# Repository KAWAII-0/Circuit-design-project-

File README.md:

# Circuit-design-project-
project for circuit design class at PUT

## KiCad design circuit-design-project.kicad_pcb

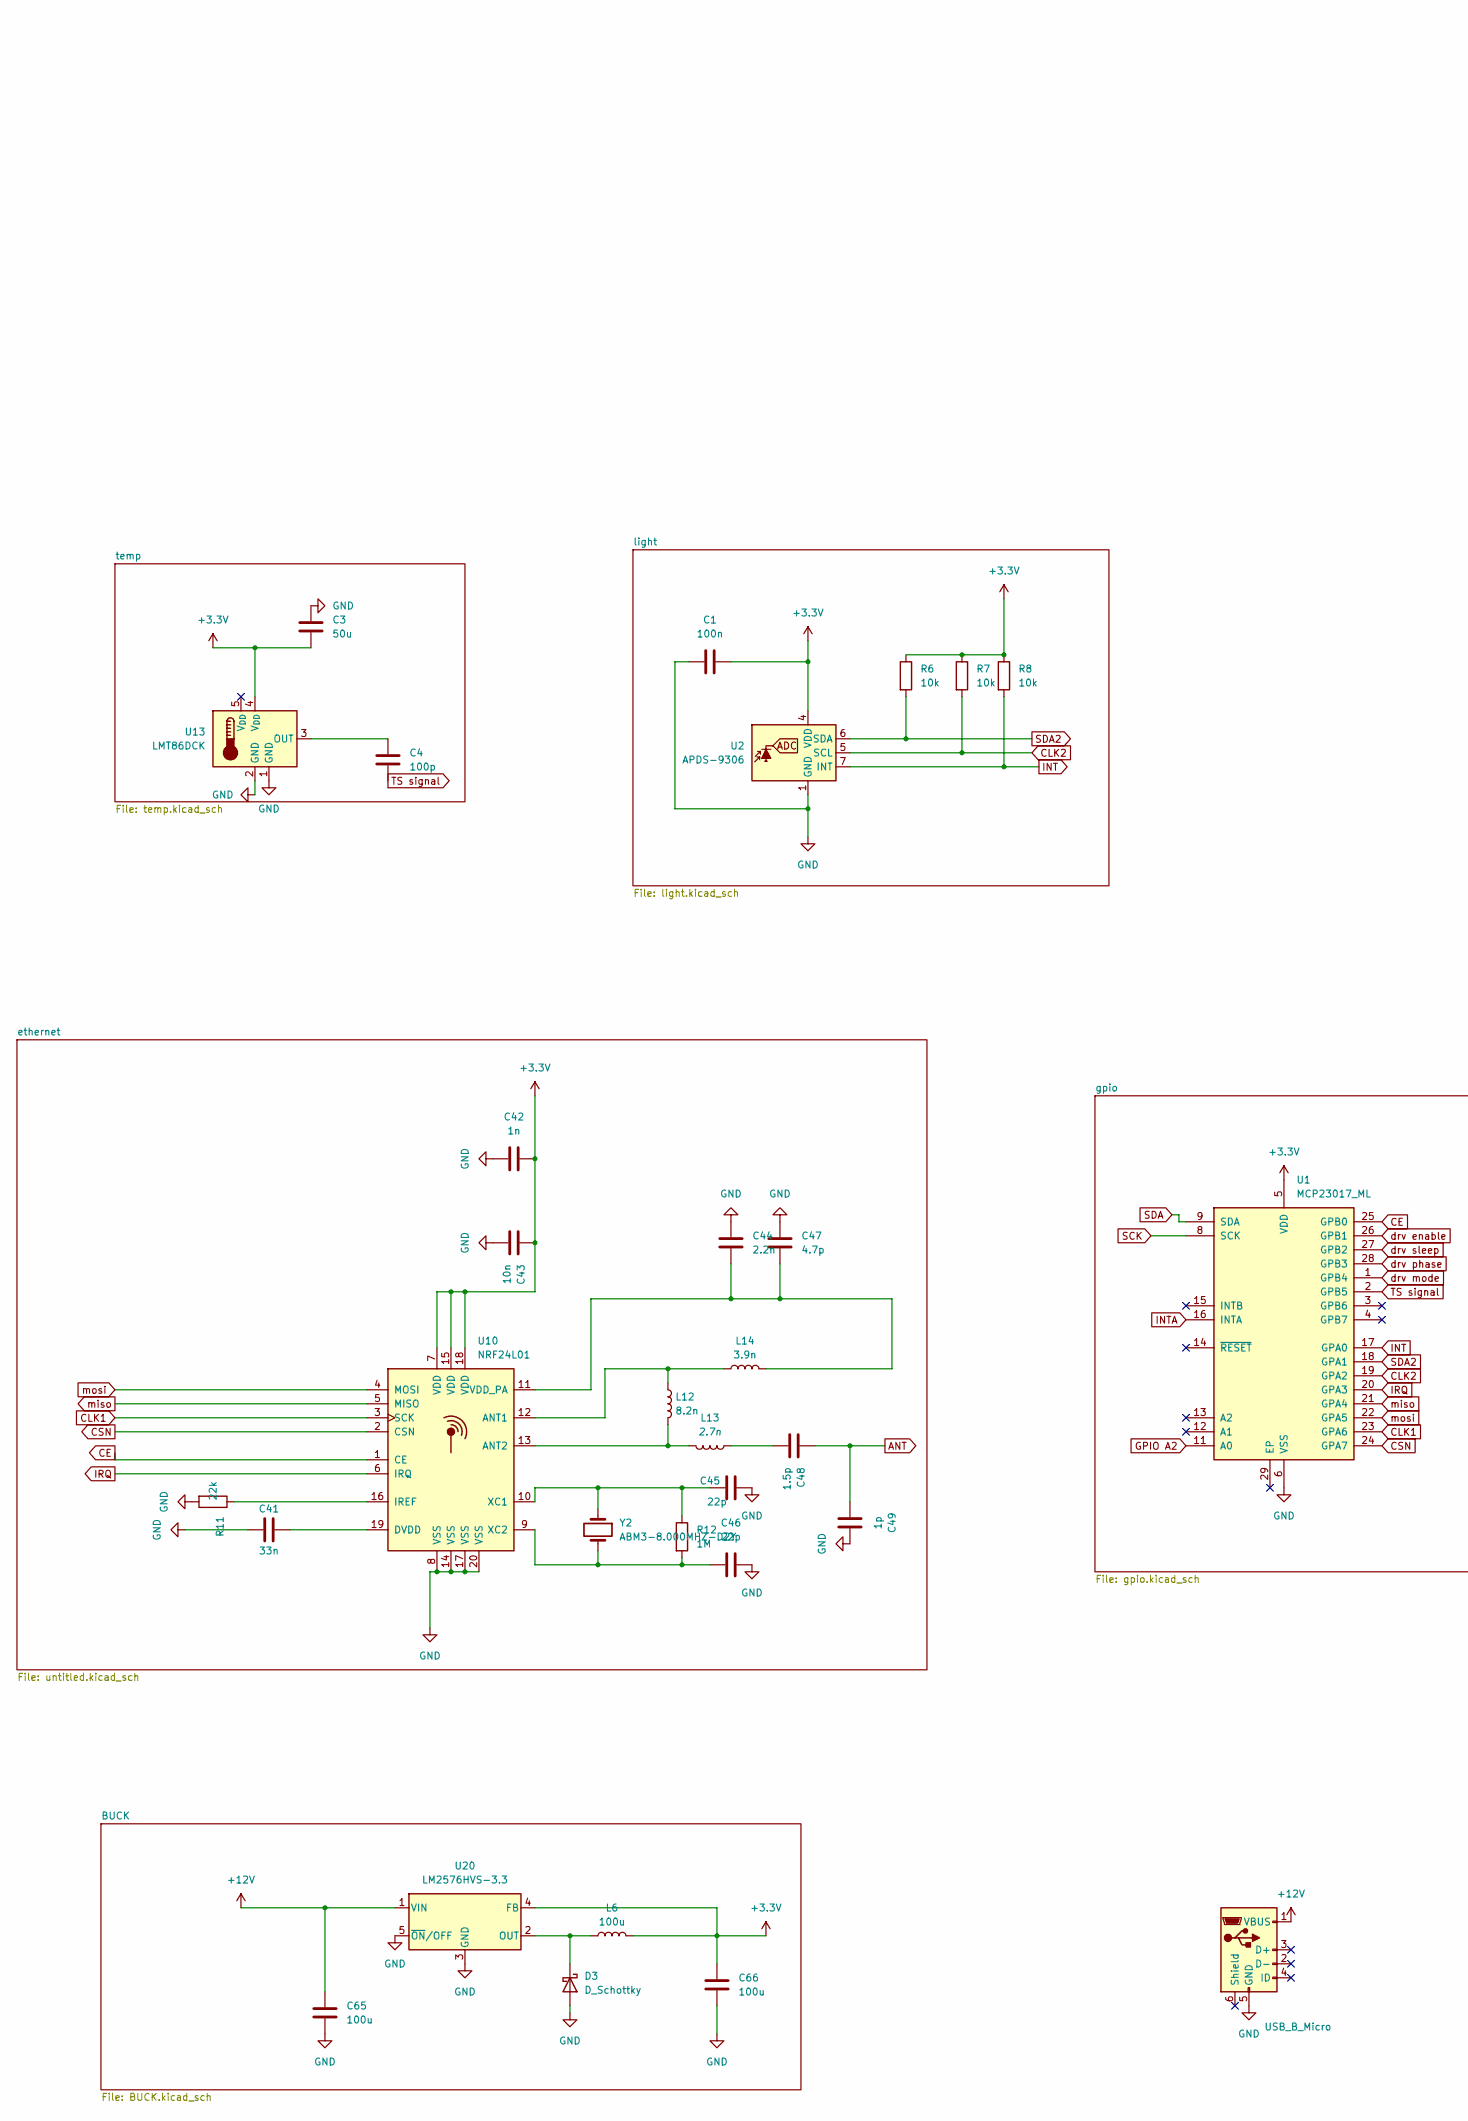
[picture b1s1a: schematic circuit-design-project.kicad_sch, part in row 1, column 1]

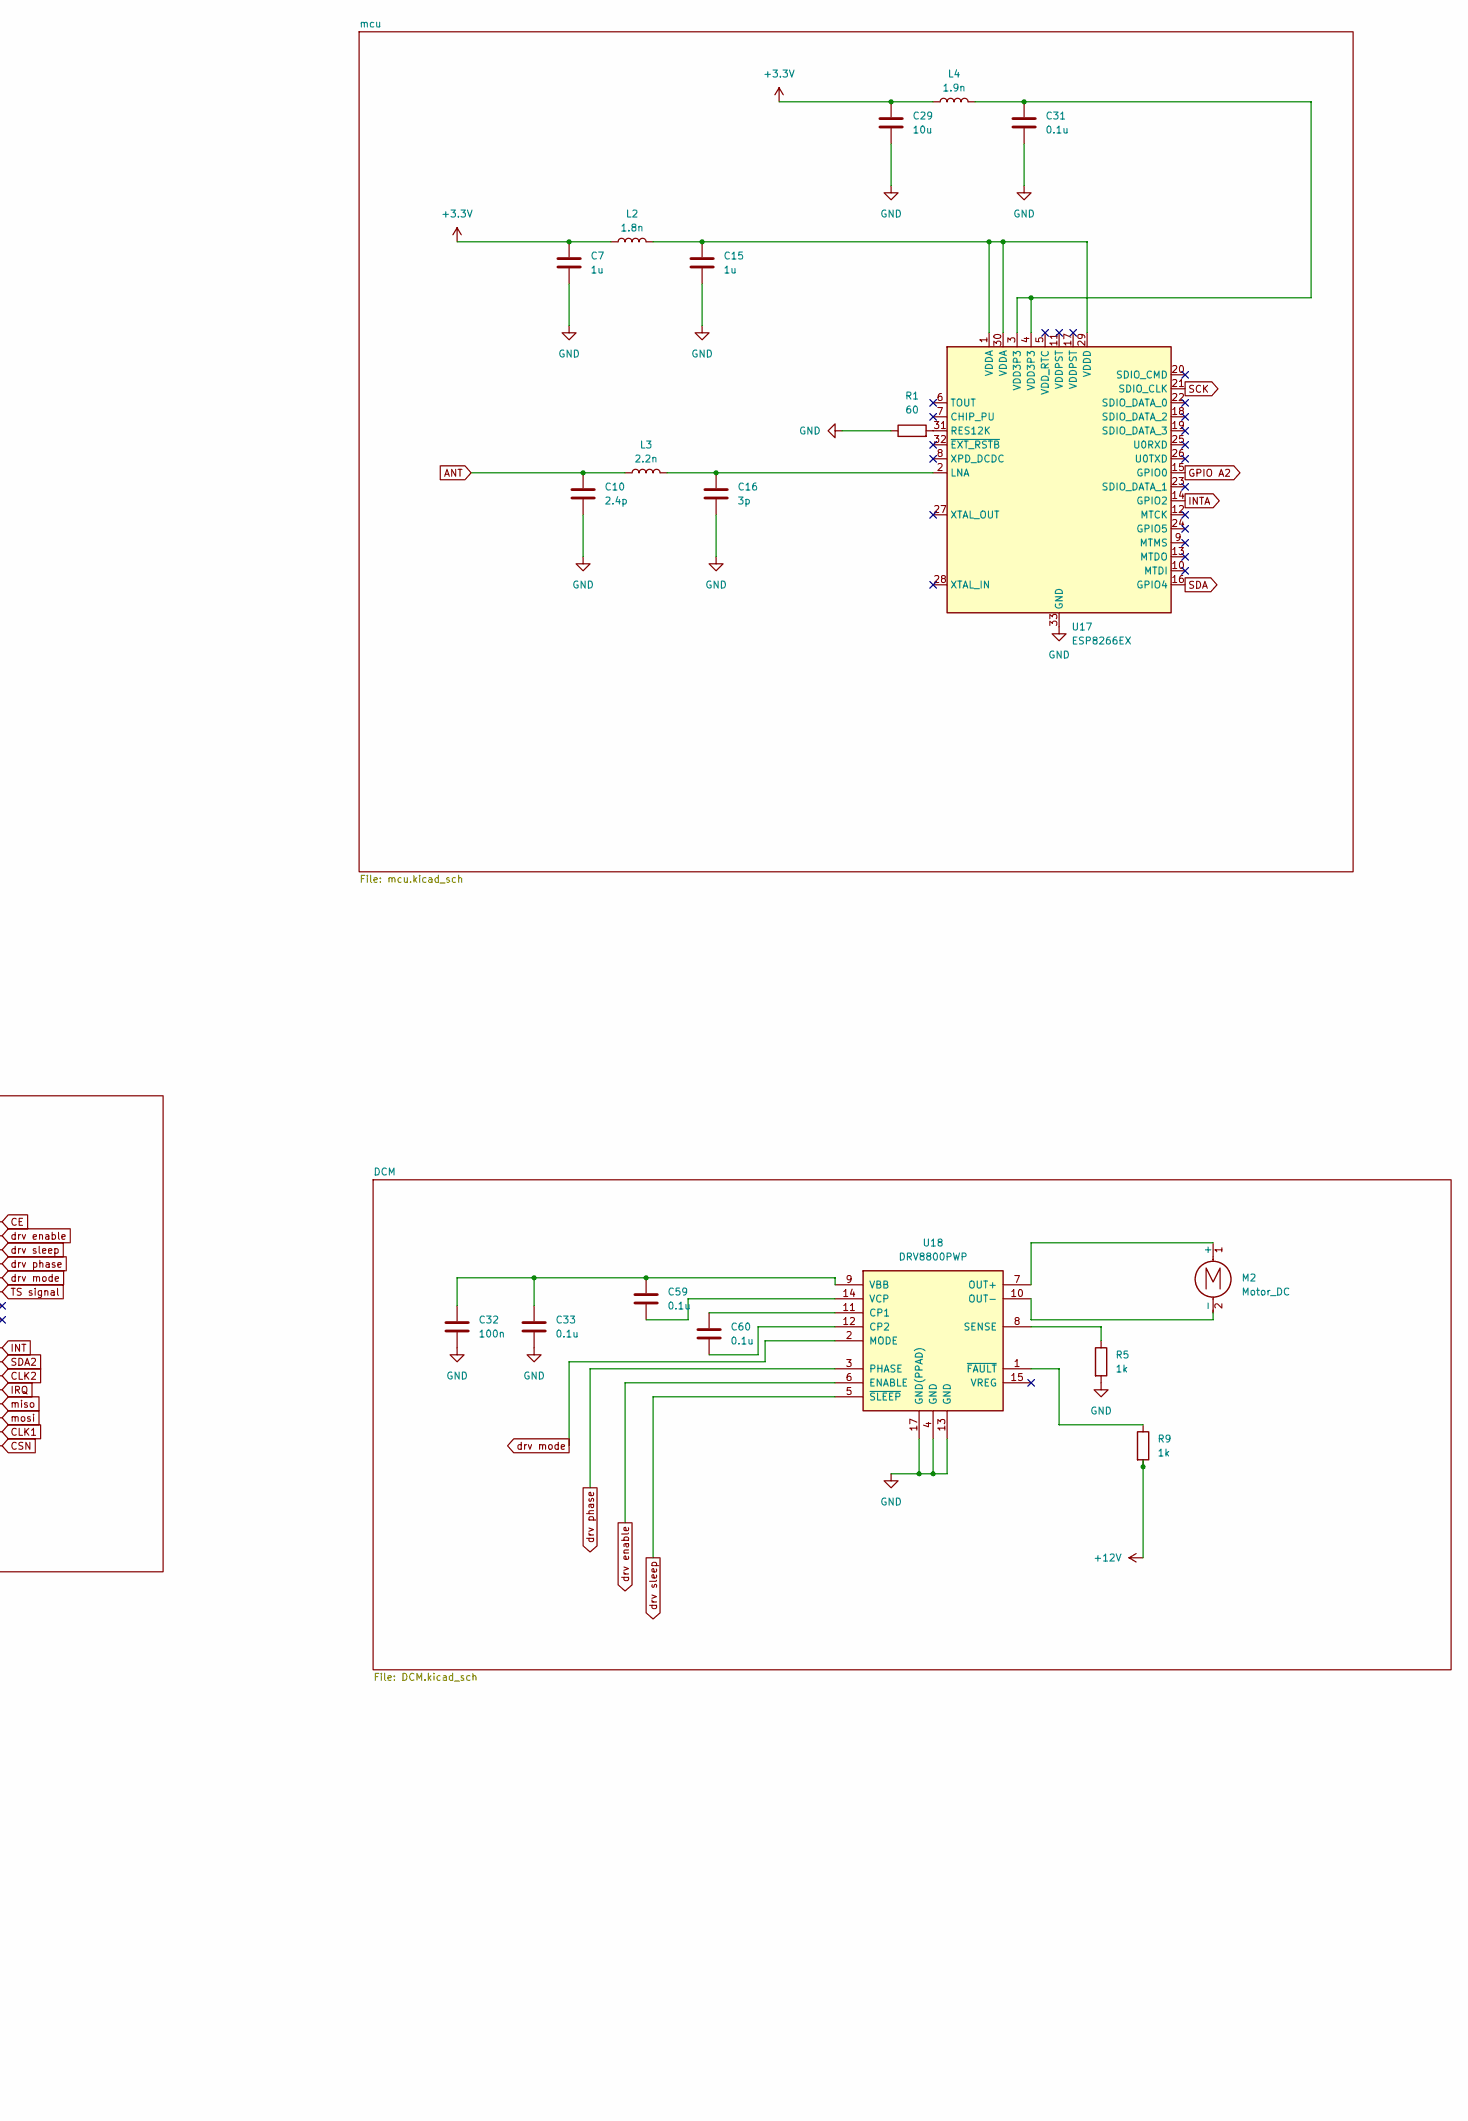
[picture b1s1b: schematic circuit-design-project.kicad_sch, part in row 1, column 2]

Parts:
C1, C32: 100n; C_0603_1608Metric
C3: 50u; C_0603_1608Metric
C4: 100p; C_0603_1608Metric
C7, C15: 1u; C_0603_1608Metric
C10: 2.4p; C_0603_1608Metric
C16: 3p; C_0603_1608Metric
C29: 10u; C_0603_1608Metric
C31, C33, C59, C60: 0.1u; C_0603_1608Metric
C41: 33n; C_0603_1608Metric
C42: 1n; C_0603_1608Metric
C43: 10n; C_0603_1608Metric
C44: 2.2n; C_0603_1608Metric
C45, C46: 22p; C_0603_1608Metric
C47: 4.7p; C_0603_1608Metric
C48: 1.5p; C_0603_1608Metric
C49: 1p; C_0603_1608Metric
C65, C66: 100u; C_0603_1608Metric
D3: D_Schottky; D_0603_1608Metric
J2: USB_B_Micro; USB_Micro-B_Wuerth_614105150721_Vertical
L2: 1.8n; L_0603_1608Metric
L3: 2.2n; L_0603_1608Metric
L4: 1.9n; L_0603_1608Metric
L6: 100u; L_0603_1608Metric
L12: 8.2n; L_0603_1608Metric
L13: 2.7n; L_0603_1608Metric
L14: 3.9n; L_0603_1608Metric
M2: Motor_DC; Vybronics_VZ30C1T8219732L
R1: 60; R_0603_1608Metric
R5, R9: 1k; R_0603_1608Metric
R6, R7, R8: 10k; R_0603_1608Metric
R11: 22k; R_0603_1608Metric
R12: 1M; R_0603_1608Metric
U1: MCP23017_ML; QFN-28-1EP_6x6mm_P0.65mm_EP4.25x4.25mm
U2: APDS-9306; Broadcom_LGA-8_2x2mm_P0.5mm
U10: NRF24L01; QFN-20-1EP_4x4mm_P0.5mm_EP2.5x2.5mm
U13: LMT86DCK; SOT-353_SC-70-5
U17: ESP8266EX; QFN-32-1EP_5x5mm_P0.5mm_EP3.45x3.45mm
U18: DRV8800PWP; HTSSOP-16-1EP_4.4x5mm_P0.65mm_EP3.4x5mm_Mask2.46x2.31mm
U20: LM2576HVS-3.3; SOT-23
Y2: ABM3-8.000MHZ-D2Y; Crystal_SMD_2012-2Pin_2.0x1.2mm

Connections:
+3.3V: C1.2, C3.2, C7.1, C29.1, C42.1, C43.1, C66.1, L2.1, L4.1, L6.2, R6.1, R7.1, R8.1, U1.5 (VDD), U2.4 (VDD), U10.7 (VDD), U10.15 (VDD), U10.18 (VDD), U13.4 (V_{DD}), U20.4 (FB)
+12V: C65.1, J2.1 (VBUS), R9.2, U20.1 (VIN)
ANT: C10.1, C48.1, C49.1, L3.1
CE: U1.25 (GPB0), U10.1 (CE)
CLK1: U1.23 (GPA6), U10.3 (SCK)
CLK2: R7.2, U1.19 (GPA2), U2.5 (SCL)
CSN: U1.24 (GPA7), U10.2 (CSN)
GND: C1.1, C3.1, C7.2, C10.2, C15.2, C16.2, C29.2, C31.2, C32.2, C33.2, C41.2, C42.2, C43.2, C44.1, C45.1, C46.2, C47.1, C49.2, C65.2, C66.2, D3.2 (A), J2.5 (GND), R1.1, R5.2, R11.2, U1.6 (VSS), U2.1 (GND), U10.8 (VSS), U10.14 (VSS), U10.17 (VSS), U10.20 (VSS), U13.1 (GND), U13.2 (GND), U17.23 (SDIO_DATA_1), U17.24 (GPIO5), U17.33 (GND), U18.4 (GND), U18.13 (GND), U18.17 (GND(PPAD)), U20.3 (GND), U20.5 (~ON/OFF)
GPIO A2: U1.11 (A0), U17.15 (GPIO0)
INT: R8.2, U1.17 (GPA0), U2.7 (INT)
INTA: U1.16 (INTA), U17.14 (GPIO2)
IRQ: U1.20 (GPA3), U10.6 (IRQ)
unnamed: C31.1, L4.2, U17.3 (VDD3P3), U17.4 (VDD3P3)
unnamed: C48.2, L13.1
unnamed: D3.1 (K), L6.1, U20.2 (OUT)
unnamed: M2.1 (+), U18.7 (OUT+)
unnamed: M2.2 (-), U18.10 (OUT-)
unnamed: L12.1, L14.1, U10.12 (ANT1)
unnamed: L12.2, L13.2, U10.13 (ANT2)
unnamed: C41.1, U10.19 (DVDD)
unnamed: R11.1, U10.16 (IREF)
unnamed: C44.2, C47.2, L14.2, U10.11 (VDD_PA)
unnamed: C45.2, R12.1, U10.10 (XC1), Y2.1
unnamed: C46.1, R12.2, U10.9 (XC2), Y2.2
unnamed: C4.1, U13.3 (OUT)
unnamed: C16.1, L3.2, U17.2 (LNA)
unnamed: R1.2, U17.31 (RES12K)
unnamed: C15.1, L2.2, U17.1 (VDDA), U17.29 (VDDD), U17.30 (VDDA)
unnamed: C60.1, U18.11 (CP1)
unnamed: C60.2, U18.12 (CP2)
unnamed: R5.1, U18.8 (SENSE)
unnamed: C32.1, C33.1, C59.1, U18.9 (VBB)
unnamed: C59.2, U18.14 (VCP)
unnamed: R9.1, U18.1 (~FAULT)
SCK: U1.8 (SCK), U17.21 (SDIO_CLK)
SDA: U1.9 (SDA), U17.16 (GPIO4)
SDA2: R6.2, U1.18 (GPA1), U2.6 (SDA)
TS signal: C4.2, U1.2 (GPB5)
drv enable: U1.26 (GPB1), U18.6 (ENABLE)
drv mode: U1.1 (GPB4), U18.2 (MODE)
drv phase: U1.28 (GPB3), U18.3 (PHASE)
drv sleep: U1.27 (GPB2), U18.5 (~SLEEP)
miso: U1.21 (GPA4), U10.5 (MISO)
mosi: U1.22 (GPA5), U10.4 (MOSI)

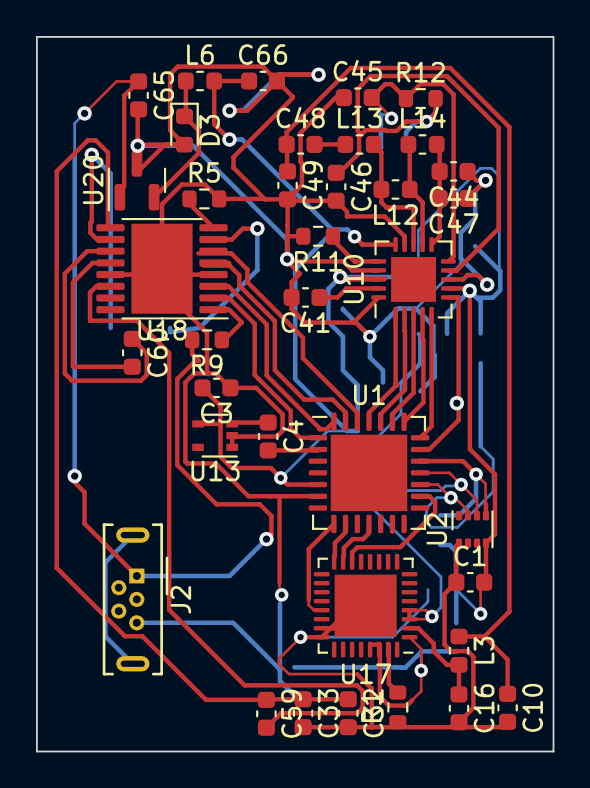
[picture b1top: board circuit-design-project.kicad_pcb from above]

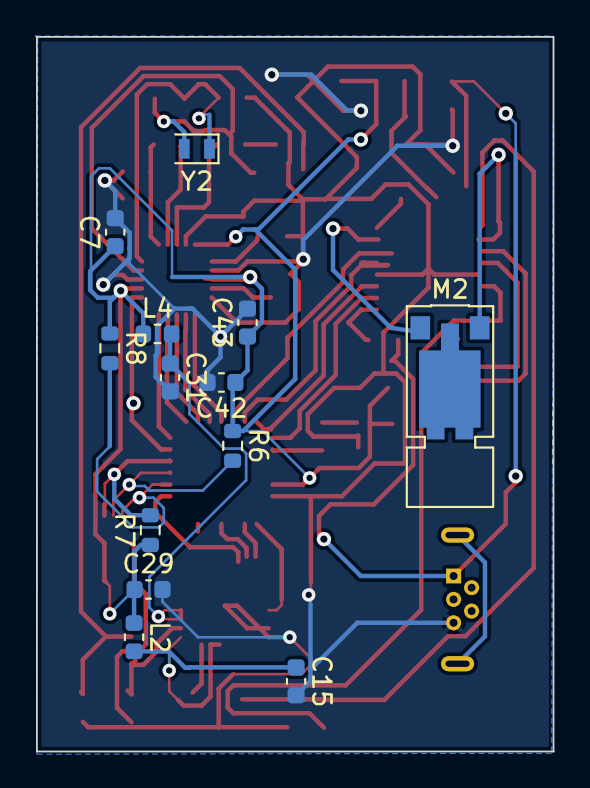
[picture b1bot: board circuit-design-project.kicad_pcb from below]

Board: 2 copper layers, 28.7 x 39.7 mm, 50 parts (13 on the bottom side), 44 nets.

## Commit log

2024-02-21 PCB
    full KiCad project for automatic rolling system
